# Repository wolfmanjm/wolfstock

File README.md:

This Delta 3D printing robot is derived from Kossel, Rostock.

It is a big bot providing about a twelve cubic inch build volume.

It uses Makerslide for the linear guides, but any 2040 extrusion with
appropriate wheels should work.

I use Misumi extrusions and brackets, and the scad files use the 3d
cad programs from Misumi for display purposes.

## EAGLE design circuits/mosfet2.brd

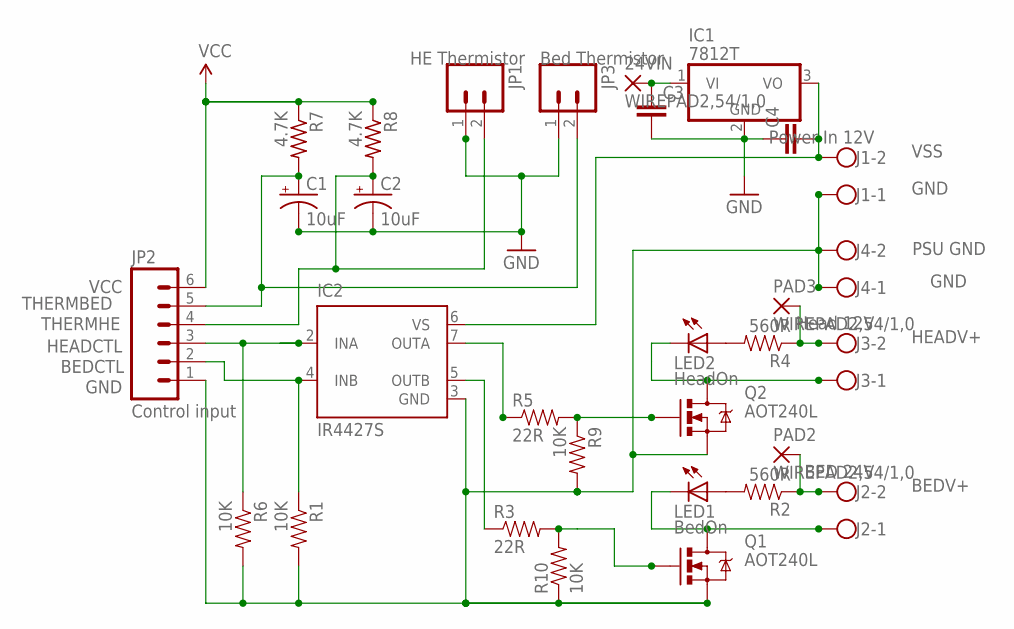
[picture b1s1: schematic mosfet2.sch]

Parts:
24VIN: WIREPAD2,54/1,0; 2,54/1,0
C1, C2: 10uF; CPOL-RADIAL-10UF-25V
C3, C4: CAPEZ; CAP-PTH-SMALLEZ
IC1: 7812T; TO220H
IC2: IR4427S; SO08
J1: Power In 12V; W237-102
J2: BED 24V; W237-102
J3: Head 12V; W237-102; MPN 237-102
J4: PSU GND; W237-102
JP1: HE Thermistor; 1X02
JP2: Control input; 1X06
JP3: Bed Thermistor; 1X02
LED1: BedOn; LED3MM-NS
LED2: HeadOn; LED3MM-NS
PAD2, PAD3: WIREPAD2,54/1,0; 2,54/1,0
Q1, Q2: AOT240L; TO220V
R1, R6, R9, R10: 10K; AXIAL-0.4
R2, R4: 560R; AXIAL-0.4
R3, R5: 22R; AXIAL-0.4
R7, R8: 4.7K; 0204/7

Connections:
BEDCTL: IC2.4 (INB), JP2.2, R1.P$1 (1)
BEDV+: J2.2, PAD2.1, R2.P$1 (1)
GND: C1.2 (-), C2.2 (-), C3.2, C4.1, IC1.2 (GND), IC2.3 (GND), J1.1, J4.1, J4.2, JP1.1, JP2.1, JP3.1, Q1.3 (S), Q2.3 (S), R1.P$2 (2), R6.P$2 (2), R9.P$2 (2), R10.P$1 (1)
HEADCTL: IC2.2 (INA), JP2.3, R6.P$1 (1)
HEADV+: J3.2, PAD3.1, R4.P$1 (1)
unnamed: 24VIN.1, C3.1, IC1.1 (VI)
unnamed: IC2.5 (OUTB), R3.P$1 (1)
unnamed: Q1.1 (G), R3.P$2 (2), R10.P$2 (2)
unnamed: LED1.A, R2.P$2 (2)
unnamed: J2.1, LED1.K (C), Q1.2 (D)
unnamed: LED2.A, R4.P$2 (2)
unnamed: Q2.1 (G), R5.P$2 (2), R9.P$1 (1)
unnamed: IC2.7 (OUTA), R5.P$1 (1)
unnamed: J3.1, LED2.K (C), Q2.2 (D)
THERMBED: C1.1 (+), JP2.5, JP3.2, R7.2
THERMHE: C2.1 (+), JP1.2, JP2.4, R8.2
VCC: JP2.6, R7.1, R8.1
VSS: C4.2, IC1.3 (VO), IC2.6 (VS), J1.2

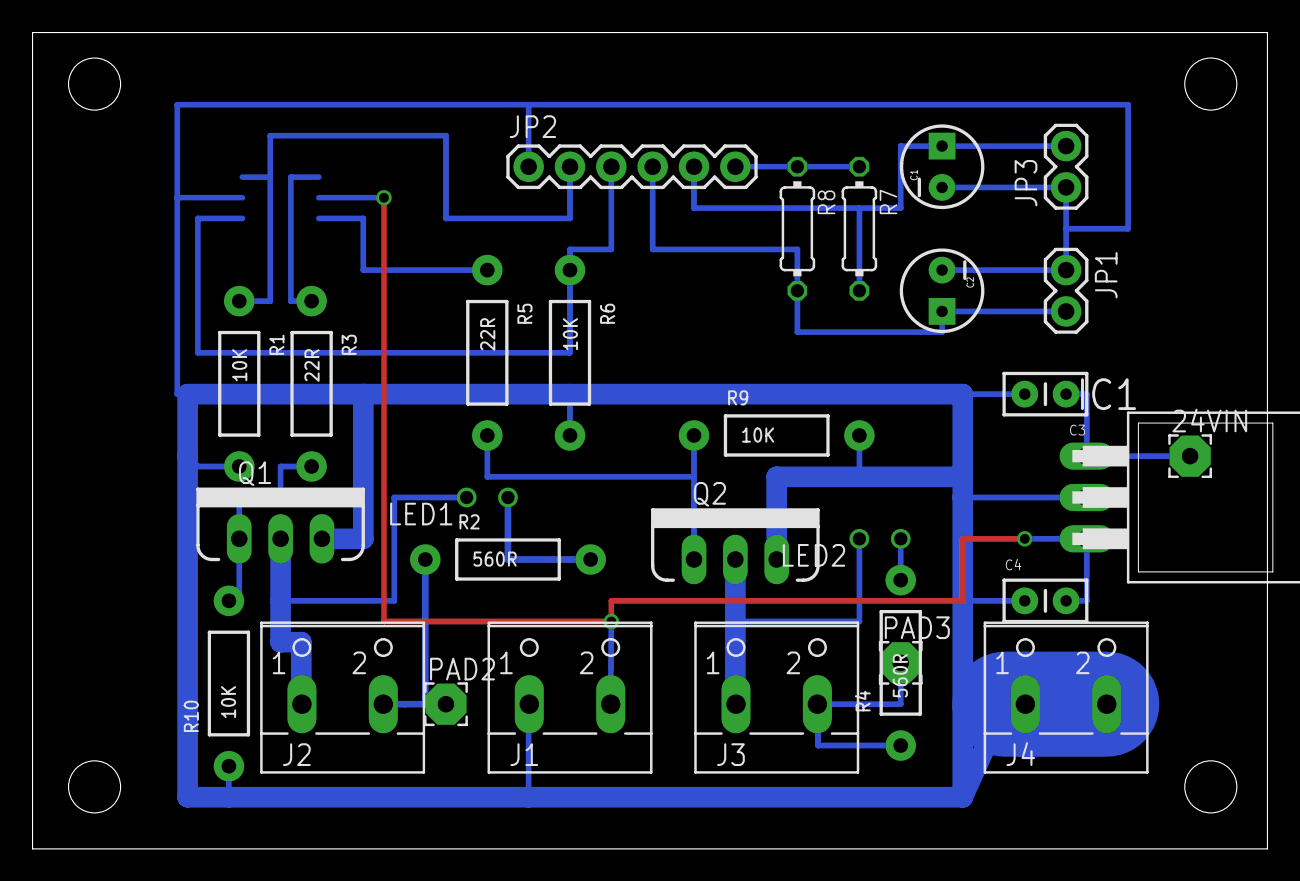
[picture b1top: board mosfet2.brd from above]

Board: 2 copper layers, 75.9 x 50.2 mm, 30 parts (1 on the bottom side), 18 nets.

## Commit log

2012-12-06 initial checkin
2012-12-06 added motor
2012-12-06 add attachment holes to motor braccket
2012-12-07 added angked plate, motor mount
2012-12-07 tweak motor mount to allow motor inside added buttress support to motors.
2012-12-23 added new files. changed tensioner to use slider profile
2013-01-07 added new files
2013-01-07 thickened arm plates added base for rod end
2013-01-07 First pages commit
2013-01-07 move gcode and stl to build
2013-01-07 reorganize
2013-01-07 fix stl locations
2013-01-07 initial githubiverse checkin
2013-01-08 add GPL license
2013-01-08 update inage
2013-01-08 add link toi gitubiverse page
2013-01-08 fix link
2013-01-09 update readme add visual of build area and round glass.
2013-01-09 change src directory
2013-01-09 added src directory which seems to be needed for githubiverse to work
2013-01-09 remove links
2013-01-09 update config
2013-01-09 fix config
2013-01-09 added grabbers idler scad
2013-01-09 Revert "Update _config.yml"
    This reverts commit 14b5ad6ae5e0bc7cee98f65979bd9e84f242e020.
2013-01-09 Revert "fix config"
    This reverts commit 7ab0aabf4c14ada5aaef19030b5b61d521076c5b.
2013-01-09 Revert "update config"
    This reverts commit 63e552c15c9d7aafee071313209e2931d3063f31.
2013-01-09 Revert "change src directory"
    This reverts commit 4d68b1afe6b1b3370dcb3418f35ec75b3299f26c.
2013-01-09 Revert "Update _config.yml"
    This reverts commit 34b2f901586fe92f00dab2ae35c623596e716eaa.
2013-01-10 beef up the angled arm plates make a print plate for them
2013-01-10 copy to src
2013-01-10 new tensioner using grabbers vwheel
2013-01-18 minor updates
2013-01-21 new parts
2013-01-21 added src
2013-03-25 added more vids
2013-03-27 update videos
2013-04-04 add circuits
2013-04-07 add back brace image
2013-06-11 update mosfet circuit
2013-06-29 added first pass at kossel-like base frame bracket
2013-06-29 completed motor bracket
2013-06-29 added overall frame
2013-06-29 turn idler sideways
2013-06-29 make motor mount holes a little bigger
2013-06-29 add calculated positioning
2013-06-29 Place all beams via calcualtions
2013-06-29 add MCAD
2013-06-29 add in build area and carriage
2013-07-01 added top bracket for 2020 using exisiting spectra idler
2013-07-01 add indent for idelr screw added image of lite frame
2013-07-01 add video
2013-07-01 Move end of beam forward to make it thicker and remove potential thin spot
2013-07-01 update stl
2013-07-02 tweak, add heated bed
2013-07-02 tweaked for old bracket size
2013-07-02 Make it bigger so traxxas can get to most of the 250mm print bed
2013-07-04 tweak
2013-07-04 Move back holes further back to make it easier to tighten
2013-07-04 updated stl too
2013-07-04 shorten bolt holes
2013-07-04 add bed bracket
2013-07-05 add top brackets
2013-07-06 add buttress to arm plate
2013-07-06 add calibration points
2013-07-09 added new carriage to hold arms
2013-07-16 removed old files
2013-07-16 point to new branch
2013-07-16 new pics
2013-07-16 added relevant src files
2013-07-16 fix stuff
2013-07-16 add new stl
2013-07-16 added BOM
2013-07-16 update bom
2013-07-18 add idler/tensioner for belt system
2013-07-19 get spacing for gt2 correct
2013-07-19 add the 608 crowned pulley
2013-07-19 add pic of belt idler
2013-07-20 Make left side of belt straight into idler
2013-07-20 Make tensioner wall thicker
2013-07-20 add belt tensioner and new arm brackets
2013-07-20 more clearance for tslot plug Increase clearance for crowned pulley
2013-07-21 start to add ability to tilt bearing shaft
2013-07-22 Add horn for bearing support
2013-07-23 strengthen eswitch holder add missing support files add an axle for the tensioner
2013-07-23 update license
2013-07-23 u[date
2013-07-23 update links in bom
2013-07-24 allow selection of makerslide or 2040
2013-07-24 increase bearing horn length add swicth for makerslide vs vslot
2013-07-24 update the src and stl dir
2013-07-24 added image of the g2 idler
2013-07-24 add images
2013-07-24 update redme to talk about the gt2 belt option
2013-07-27 first pass at a gt2 belt carriage
2013-07-29 add obligaroty sample card object
2013-07-30 added bolt lengths to readme
2013-07-30 fix molt size
2013-07-30 update bo,t lengths
2013-07-30 correct bolt lengths again
2013-08-01 add construction to readme
2013-08-08 added the peng[os and vikilcd brackets/box new video
2013-08-09 updated readme and added a video made crowned pulley more "crowned"
2013-08-10 check belt clearnce with 0.25" spacers
2013-08-10 make gt2 tensioner longer to increase clearance from carriage to a tad over 1mm
2013-08-10 Make crowned pulley exactly same width as 608 bearing so it fits housing
2013-08-11 add new idler/tensioner using back to back F695zz flanged bearings
2013-08-11 update readme file to cover the gt2 belt drive and sources
2013-08-11 fix readme
2013-08-11 added new fles to src and stl
2013-08-12 another go at belt clamps on the carriage
2013-08-12 third try at belt terminations for carriage, this one is a simple M3 reinforced post
2013-08-16 added alternative CF tube source
2013-08-17 added carriage plate and arm mount combined
2013-08-20 tweak wheel distance
2013-08-21 added tray for smoothie board
2013-08-21 use oins for smoothie board make belt pillars thicker add some extra support for the horns
2013-08-21 use pins to hold smoothie rather than screws
2013-08-25 added a paramatric conical spool holder
2013-08-26 added example picture
2013-09-03 add link to extruder I use
2013-09-05 added latest gt2 carriage for mounting on carriage plate
2013-09-05 beefed up a bit
2013-09-06 repair carriage plate
2013-11-24 update source and stl
2013-11-26 u[date license
2014-02-27 update readme, go from WIP to stable
2014-05-02 make endstop stick out further
2014-05-15 make effector a little more robust
2015-06-17 new effector

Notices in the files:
parts and their libraries:
SparkFun-LED: Licensing: CC v3.0 Share-Alike You are welcome to use this library for commercial purposes.
